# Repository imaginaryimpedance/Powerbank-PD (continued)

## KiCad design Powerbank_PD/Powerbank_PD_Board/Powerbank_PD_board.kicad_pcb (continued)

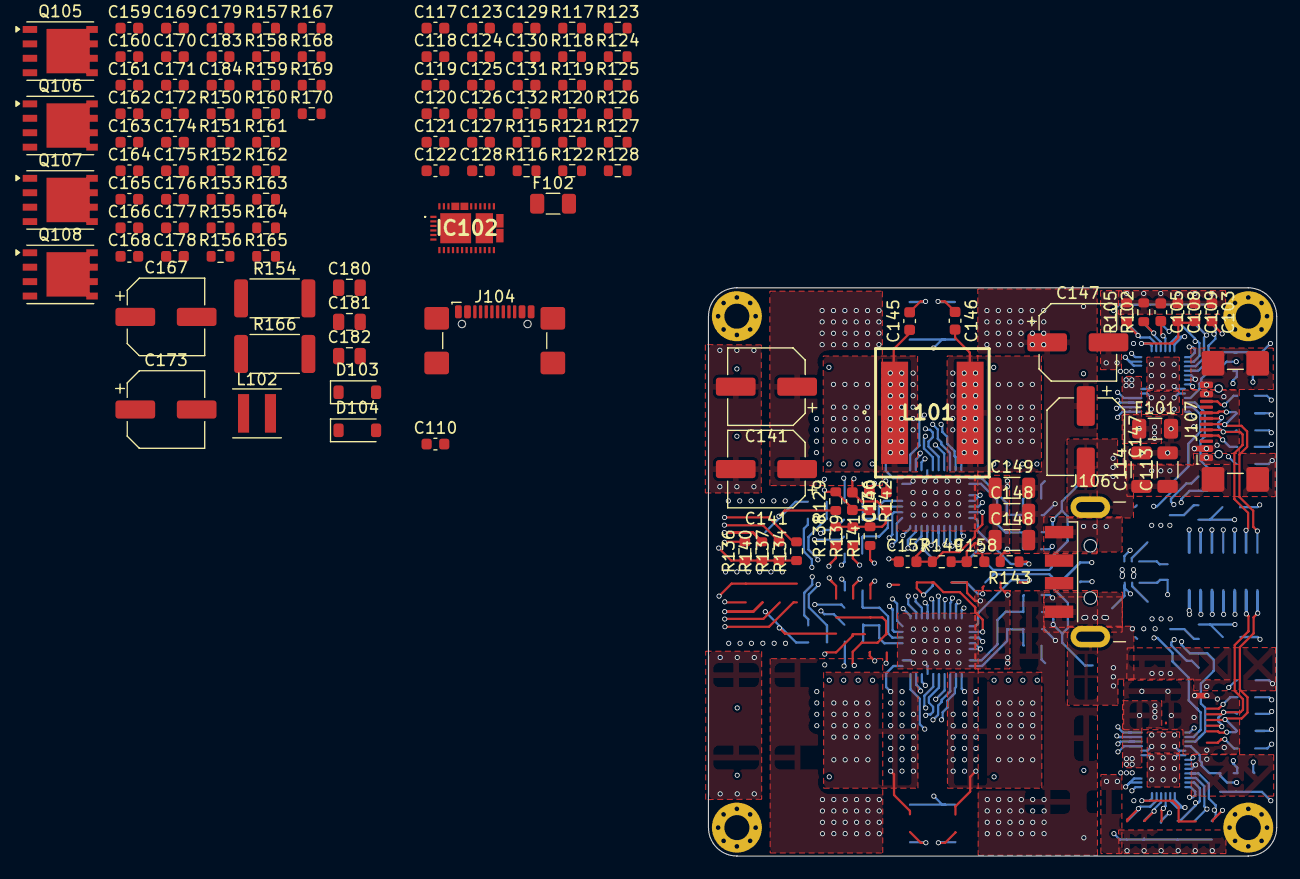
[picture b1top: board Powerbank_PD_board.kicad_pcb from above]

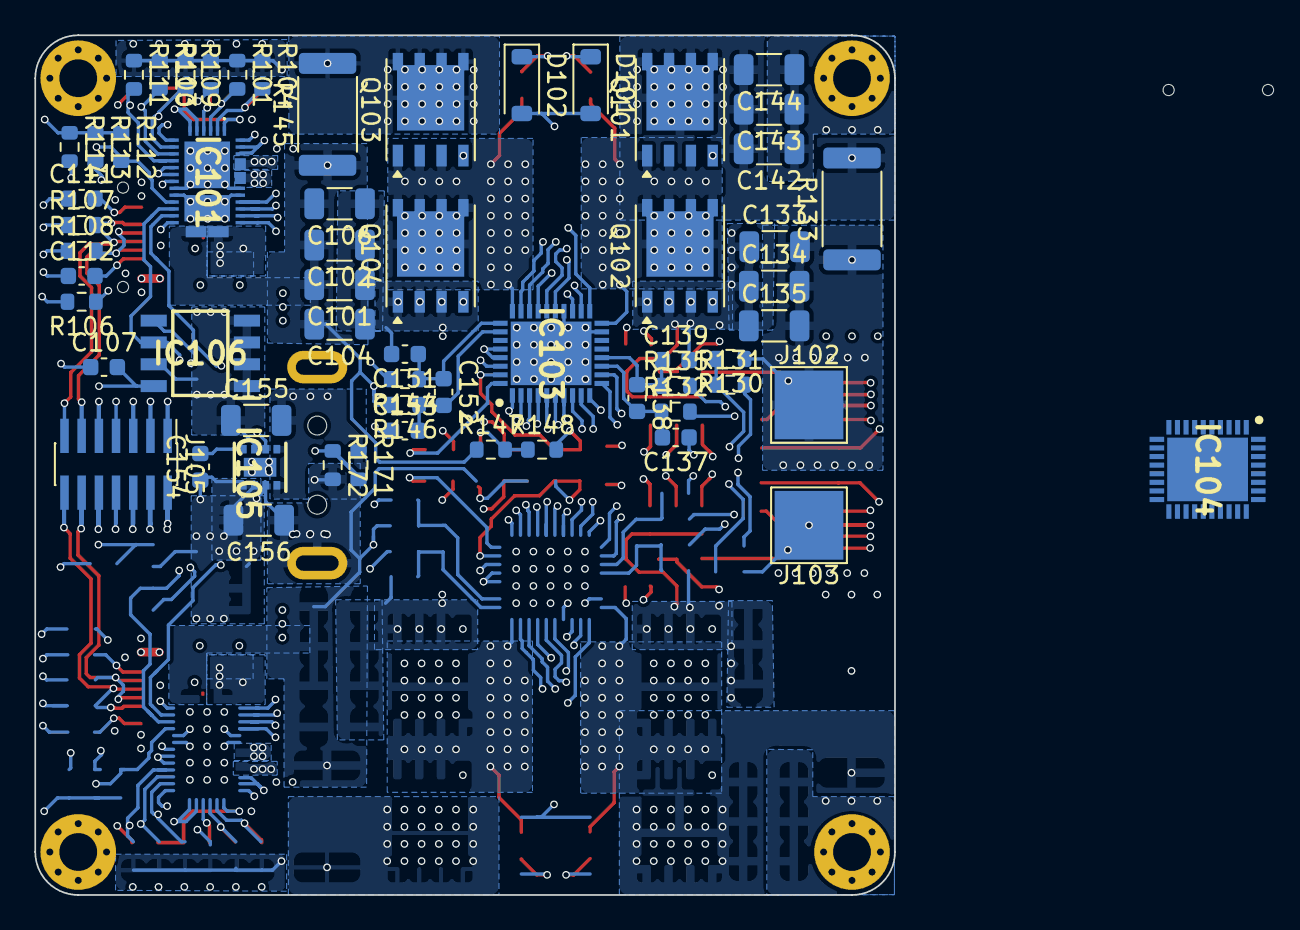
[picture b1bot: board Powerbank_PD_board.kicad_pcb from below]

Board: 6 copper layers, 50.0 x 50.0 mm, 184 parts (60 on the bottom side), 106 nets.

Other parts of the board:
C141#2, C147#2: 100u; CP_Elec_6.3x7.7
C148#2: 10u; C_1206_3216Metric

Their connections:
GND: C141#2.2, C147#2.2, C148#2.1; also elsewhere on the board
unnamed 99: C141#2.1; also elsewhere on the board
unnamed 100: C147#2.1, C148#2.2; also elsewhere on the board
